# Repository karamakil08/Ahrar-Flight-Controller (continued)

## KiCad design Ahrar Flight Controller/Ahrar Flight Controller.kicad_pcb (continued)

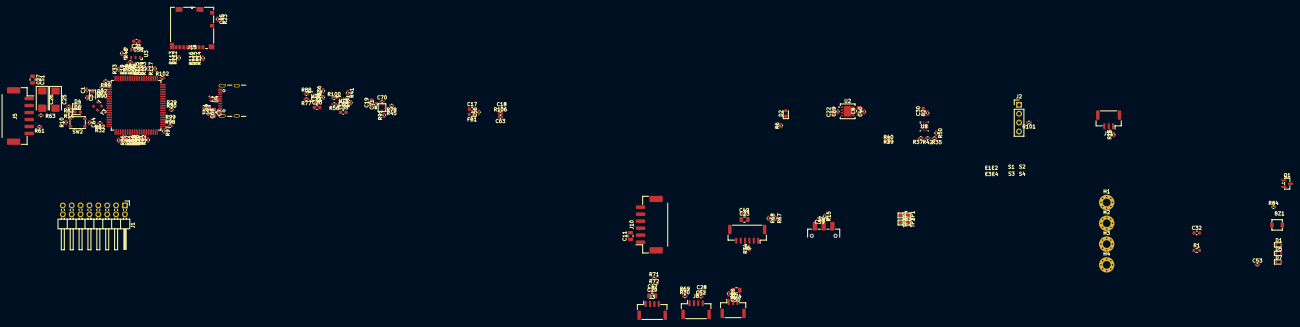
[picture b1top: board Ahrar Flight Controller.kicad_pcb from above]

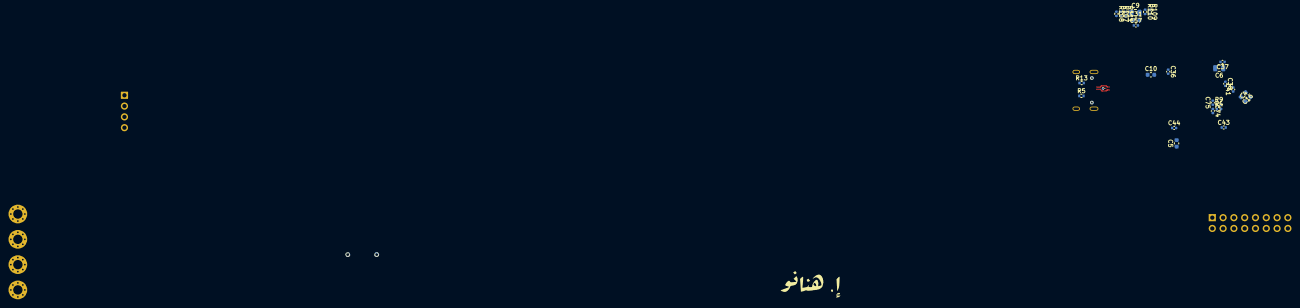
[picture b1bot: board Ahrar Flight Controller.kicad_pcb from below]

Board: 4 copper layers, 182 parts (26 on the bottom side), 142 nets.

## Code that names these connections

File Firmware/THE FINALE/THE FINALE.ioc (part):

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Mcu.Name=STM32H743VITx
Mcu.Package=LQFP100
Mcu.UserName=STM32H743VITx
PA0.GPIOParameters=GPIO_Label
PA0.GPIO_Label=RF_CTS
PA0.Mode=CTS_RTS
PA0.Signal=USART2_CTS
PA1.GPIOParameters=GPIO_Label
PA1.GPIO_Label=RF_RTS
PA1.Mode=CTS_RTS
PA1.Signal=USART2_RTS
PA11.Mode=Device_Only
PA11.Signal=USB_OTG_FS_DM
PA12.Mode=Device_Only
PA12.Signal=USB_OTG_FS_DP
PA13\ (JTMS/SWDIO).Mode=Serial_Wire
PA13\ (JTMS/SWDIO).Signal=DEBUG_JTMS-SWDIO
PA14\ (JTCK/SWCLK).Mode=Serial_Wire
PA14\ (JTCK/SWCLK).Signal=DEBUG_JTCK-SWCLK
PA2.GPIOParameters=GPIO_Label
PA2.GPIO_Label=RF_TX
PA2.Mode=Asynchronous
PA2.Signal=USART2_TX
PA3.GPIOParameters=GPIO_Label
PA3.GPIO_Label=RF_RX
PA3.Mode=Asynchronous
PA3.Signal=USART2_RX
PA4.GPIOParameters=GPIO_Label
PA4.GPIO_Label=ICM86_INT
PA4.Signal=GPIO_Input
PA5.GPIOParameters=GPIO_Label
PA5.GPIO_Label=ICM86_SCK
PA5.Mode=Full_Duplex_Master
PA5.Signal=SPI1_SCK
PA6.GPIOParameters=GPIO_Label
PA6.GPIO_Label=ICM86_MISO
PA6.Mode=Full_Duplex_Master
PA6.Signal=SPI1_MISO
PA7.GPIOParameters=GPIO_Label
PA7.GPIO_Label=ICM86_MOSI
PA7.Mode=Full_Duplex_Master
PA7.Signal=SPI1_MOSI
PB0.GPIOParameters=GPIO_Label
PB0.GPIO_Label=SERVO1
PB0.Signal=S_TIM3_CH3
PB1.GPIOParameters=GPIO_Label
PB1.GPIO_Label=SERVO2
PB1.Signal=S_TIM3_CH4
PB10.GPIOParameters=GPIO_Label
PB10.GPIO_Label=Pitot_SCL
PB10.Mode=I2C
PB10.Signal=I2C2_SCL
PB11.GPIOParameters=GPIO_Label
PB11.GPIO_Label=Pitot_SDA
PB11.Mode=I2C
PB11.Signal=I2C2_SDA
PB12.GPIOParameters=GPIO_Label
PB12.GPIO_Label=ICM88_SS
PB12.Signal=GPIO_Output
PB13.GPIOParameters=GPIO_Label
PB13.GPIO_Label=ICM88_SCK
PB13.Mode=Full_Duplex_Master
PB13.Signal=SPI2_SCK
PB14.GPIOParameters=GPIO_Label
PB14.GPIO_Label=ICM88_MISO
PB14.Mode=Full_Duplex_Master
PB14.Signal=SPI2_MISO
PB15.GPIOParameters=GPIO_Label
PB15.GPIO_Label=ICM88_MOSI
PB15.Mode=Full_Duplex_Master
PB15.Signal=SPI2_MOSI
PB3\ (JTDO/TRACESWO).GPIOParameters=GPIO_Label
PB3\ (JTDO/TRACESWO).GPIO_Label=MS_SCK
PB3\ (JTDO/TRACESWO).Mode=Full_Duplex_Master
PB3\ (JTDO/TRACESWO).Signal=SPI3_SCK
PB4\ (NJTRST).GPIOParameters=GPIO_Label
PB4\ (NJTRST).GPIO_Label=MS_MISO
PB4\ (NJTRST).Mode=Full_Duplex_Master
PB4\ (NJTRST).Signal=SPI3_MISO
PB5.GPIOParameters=GPIO_Label
PB5.GPIO_Label=MS_MOSI
PB5.Mode=Full_Duplex_Master
PB5.Signal=SPI3_MOSI
PB6.GPIOParameters=GPIO_Label
PB6.GPIO_Label=AUX_TX
PB6.Mode=Asynchronous
PB6.Signal=USART1_TX
PB7.GPIOParameters=GPIO_Label
PB7.GPIO_Label=AUX_RX
PB7.Mode=Asynchronous
PB7.Signal=USART1_RX
PB8.GPIOParameters=GPIO_Label
PB8.GPIO_Label=Compass_SCL
PB8.Mode=I2C
PB8.Signal=I2C1_SCL
PB9.GPIOParameters=GPIO_Label
PB9.GPIO_Label=Compass_SDA
PB9.Mode=I2C
PB9.Signal=I2C1_SDA
PC0.GPIOParameters=GPIO_Label
PC0.GPIO_Label=RED_LED
PC0.Signal=GPIO_Output
PC1.GPIOParameters=GPIO_Label
PC1.GPIO_Label=BLUE_LED
PC1.Signal=GPIO_Output
PC10.Mode=SD_4_bits_Wide_bus
PC10.Signal=SDMMC1_D2
PC11.Mode=SD_4_bits_Wide_bus
PC11.Signal=SDMMC1_D3
PC12.Mode=SD_4_bits_Wide_bus
PC12.Signal=SDMMC1_CK
PC14-OSC32_IN\ (OSC32_IN).Mode=LSE-External-Oscillator
PC14-OSC32_IN\ (OSC32_IN).Signal=RCC_OSC32_IN
PC15-OSC32_OUT\ (OSC32_OUT).Mode=LSE-External-Oscillator
PC15-OSC32_OUT\ (OSC32_OUT).Signal=RCC_OSC32_OUT
PC2_C.GPIOParameters=GPIO_Label
PC2_C.GPIO_Label=Voltage_Sense
PC2_C.Signal=GPIO_Analog
PC3_C.GPIOParameters=GPIO_Label
PC3_C.GPIO_Label=Current_Sense
PC3_C.Signal=GPIO_Analog
PC4.GPIOParameters=GPIO_Label
PC4.GPIO_Label=ICM86_SS
PC4.Signal=GPIO_Output
PC6.GPIOParameters=GPIO_Label
PC6.GPIO_Label=Buzzer
PC6.Signal=S_TIM8_CH1
PC8.Mode=SD_4_bits_Wide_bus
PC8.Signal=SDMMC1_D0
PC9.Mode=SD_4_bits_Wide_bus
PC9.Signal=SDMMC1_D1
PD1.GPIOParameters=GPIO_Label
PD1.GPIO_Label=SD_CD
PD1.Signal=GPIO_Input
PD12.GPIOParameters=GPIO_Label
PD12.GPIO_Label=LIDAR_SCL
PD12.Mode=I2C
PD12.Signal=I2C4_SCL
PD13.GPIOParameters=GPIO_Label
PD13.GPIO_Label=LIDAR_SDA
PD13.Mode=I2C
PD13.Signal=I2C4_SDA
PD14.GPIOParameters=GPIO_Label
PD14.GPIO_Label=SERVO3
PD14.Signal=S_TIM4_CH3
PD15.GPIOParameters=GPIO_Label
PD15.GPIO_Label=SERVO4
PD15.Signal=S_TIM4_CH4
PD2.Mode=SD_4_bits_Wide_bus
PD2.Signal=SDMMC1_CMD
PD4.GPIOParameters=GPIO_Label
PD4.GPIO_Label=GPIO1
PD4.Signal=GPIO_Output
PD5.GPIOParameters=GPIO_Label
PD5.GPIO_Label=GPIO2
PD5.Signal=GPIO_Output
PD6.GPIOParameters=GPIO_Label
PD6.GPIO_Label=GPIO3
PD6.Signal=GPIO_Output
PD7.GPIOParameters=GPIO_Label
PD7.GPIO_Label=MS_SS
PD7.Signal=GPIO_Output
PD8.GPIOParameters=GPIO_Label
PD8.GPIO_Label=ICM88_INT
PD8.Signal=GPIO_Input
PD9.GPIOParameters=GPIO_Label
PD9.GPIO_Label=SBUS_RX
PD9.Signal=USART3_RX
PE0.GPIOParameters=GPIO_Label
PE0.GPIO_Label=GPS_RX
PE0.Mode=Asynchronous
PE0.Signal=UART8_RX
PE1.GPIOParameters=GPIO_Label
PE1.GPIO_Label=GPS_TX
PE1.Mode=Asynchronous
PE1.Signal=UART8_TX
PE11.GPIOParameters=GPIO_Label
PE11.GPIO_Label=ESC2
PE11.Signal=S_TIM1_CH2
PE13.GPIOParameters=GPIO_Label
PE13.GPIO_Label=ESC3
PE13.Signal=S_TIM1_CH3
PE14.GPIOParameters=GPIO_Label
PE14.GPIO_Label=ESC4
PE14.Signal=S_TIM1_CH4
PE2.GPIOParameters=GPIO_Label
PE2.GPIO_Label=BMP_SCK
PE2.Mode=Full_Duplex_Master
PE2.Signal=SPI4_SCK
PE3.GPIOParameters=GPIO_Label
PE3.GPIO_Label=BMP_INT
PE3.Signal=GPIO_Input
PE4.GPIOParameters=GPIO_Label
PE4.GPIO_Label=BMP_SS
PE4.Signal=GPIO_Output
PE5.GPIOParameters=GPIO_Label
PE5.GPIO_Label=BMP_MISO
PE5.Mode=Full_Duplex_Master
PE5.Signal=SPI4_MISO
PE6.GPIOParameters=GPIO_Label
PE6.GPIO_Label=BMP_MOSI
PE6.Mode=Full_Duplex_Master
PE6.Signal=SPI4_MOSI
PE9.GPIOParameters=GPIO_Label
PE9.GPIO_Label=ESC1
PE9.Signal=S_TIM1_CH1
PH0-OSC_IN\ (PH0).Mode=HSE-External-Oscillator
PH0-OSC_IN\ (PH0).Signal=RCC_OSC_IN
PH1-OSC_OUT\ (PH1).Mode=HSE-External-Oscillator
PH1-OSC_OUT\ (PH1).Signal=RCC_OSC_OUT
RCC.SYSCLKFreq_VALUE=480000000
RCC.SYSCLKSource=RCC_SYSCLKSOURCE_PLLCLK
board=custom
